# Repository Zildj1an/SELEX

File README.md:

# SELEX Process with Artificial Intelligence 👨‍🔧

## [0] Introduction 📄

This was a long project that involved:

 * [1] The robotic automatization of biotechnological protocols.
 
      All the custom hardware design can be found at OT_Robot/harware_design.
 * [2] The usage of Artifical Intelligence.
 * [3] A search engine.
 * [4] A tool to migrate WordPress websites to the iGem servers.
 * [5] And many, many custom hardware.

You can find information on installation and usage at the end [5] and our <a href = "https://2019.igem.org/Team:MADRID_UCM/Hardware">website</a>.

## [1] Biotechnological Designs 🔬

Folder OT_Robot contains biotechnological protocols for obtaining trained libraries of DNA aptamer molecules automated with the Opentrons OT-2 robot. This protocol is part of our contribution to the 2019 iGEM international biotechnology competition. For the thermocycler we built the Ninja-PCR(original from [hisashin](https://github.com/hisashin/NinjaPCR/)). More information about the entire project can be found in our <a href = "https://2019.igem.org/Team:MADRID_UCM/Landing">website</a>.

Aptamers are a cutting-edge technology that is revolutionizing biotechnology, from biosensing to synthetic biology. Aptamers are single-strand DNA molecules that hold nature’s most important information: our genetic code. But instead of using DNA for carrying information, our aptamers depend on DNA’s 3-dimensional shape. 

We genetically engineer this shape to take hold of and mesh with our target molecule. DNA’s unique role in nature gives aptamers amazing characteristics, making them robust, stable, and cheap to produce. 

The small-sized thermal cycler is controlled via motherboard Ninja-PCR Arduino-alike, as shown above, manually welded, whose code is in NinjaPCR [folder](https://github.com/Zildj1an/SELEX/tree/master/NinjaPCR). You can update a new binary since ESP8266 SystemOnChip includes the TCP/IP stack. We also recommend the usage of an external Raspberry Pi to uninterruptedly provide the robot with Wi-Fi. You can find more information about usage at [5].

## [2] Artificial Intelligence Algorithm: GAN network 🤖

We also did an **Artificial Intelligence algorithm** to predict the optimal DNA molecule shapes. It is a Generative adversarial network, divided in two neuronal networks: the Generative and the Discriminative. CNN nets are used. 

## [3] iGem Search Engine 🔍 

In addition, you can use our Search Engine for words in previous or this year's team's websites. This is a python search engine with GUI for searching words in each competition year and team's website.

# [4] A tool to migrate WordPress websites to the iGem servers.

We also developed a tool to make life easier to web page developers at the iGem competition. You can use WordPress templates to develop your site and then migrate it easily with this multi-threaded script located at Tool_Migrate folder.

To run the script you can do:

```
$ bash treatment.sh [url_1] -nm - - [url_2]
```

Some additional options are available, feel free to navigate throw our code!

# [5] Hardware Design 🔋 

## Potentiostat

To assemble the potentiostat, first you should send to manufacture the PCB, in our instance we sent it to JLPCB (https://jlcpcb.com/) and buy the components listed on the Bill of Materials file. After that, you should solder those materials on the PCB. You can also request them to solder the components, if they have them.

Any team could reproduce this potentiostat sending the gerber and the NC Drill files to the manufacturer.

Regarding to the case, we designed it with a 3D modelling software, and we cut the flat faces in methacrylate with a laser cutter machine and otherwise we printed it with a 3D printer.

The PCB was made with the Altium Designer software. Altium can export PCB and schematic files as ACCEL-ASCII files. With these files you can import them to Eagle.

## Fluorimeter
To assemble the fluorimeter, you should send to manufacture the PCB, for instance we sent it to JLPCB (https://jlcpcb.com/) and buy the components listed on the Bill of Materials file. After that, you should solder those materials on the PCB. You can also request them to solder the components, if they have them.

Any team could reproduce this fluorimeter sending the gerber and the NC Drill files to the manufacturer. The PCB was made with the Altium Designer software. Altium can export PCB and schematic files as ACCEL-ASCII files. With these files you can import them to Eagle.

In relation to the case, we designed it with a 3D modelling software, and we cut the faces in methacrylate with a laser cutter machine.

## Wax Module
Wax Module
To assemble the Wax Module, you should send to manufacture the PCB, in our instance we sent it to JLPCB (https://jlcpcb.com/) and buy the components listed on the Bill of Materials file. After that, you should solder those materials on the PCB. You can also request them to solder the components, if they have them.

Any team could reproduce this module sending the gerber and the NC Drill files to the manufacturer.

The PCB was made with the Eagle software. To generate the necessary files, you can follow the JLPCB guide (https://support.jlcpcb.com/article/43-how-to-export-eagle-pcb-to-gerber-files).

In relation to the case, we designed it with a 3D modelling software, and we cut the faces with a laser cutter and the part where the resistances are located, was printed with an aluminium printer. Also, the part where the stamps are placed can be printed with a 3D printer.

## PCR, Thermal Modules
To assemble the NinjaPCR, you can make it yourself following the instructions written on their webpage or buy it (https://ninjapcr.tori.st/en/index.html).

To assemble the Thermal Module, you can send to manufacture the PCB, in our instance we sent it to JLPCB (https://jlcpcb.com/) and buy the components listed on the Bill of Materials file. After that, you should solder those materials on the PCB. You can also request them to solder the components, if they have them. The other option you could buy it from their webpage.

In relation to the case, we redesigned the NinjaPCR case with a 3D modelling software, and we cut the faces with a laser cutter in methacrylate and in wood. 

We redesigned it because we used another fan.

## Shaker Module
To assemble the Shaker Module, you should send to manufacture the PCB, in our instance we sent it to JLPCB (https://jlcpcb.com/) and buy the components listed on the Bill of Materials file. After that, you should solder those materials on the PCB. You can also request them to solder the components, if they have them.

Any team could reproduce this module sending the gerber and the NC Drill files to the manufacturer.

The PCB was made with the Eagle software. To generate the necessary files, you can follow the JLPCB guide (https://support.jlcpcb.com/article/43-how-to-export-eagle-pcb-to-gerber-files).

In relation to the case, we designed it with a 3D modelling software, and we printed the module with a 3D printer.

We also designed some PCBs from ourselves to make things easier and make them fit in the robot. We used a 3D-printer for some of our designs to store Eppendorf and Falcon tipracks. We also deisgned a PCB for a potenciostat microcontroller Teensy 3.0 and an auxiliar thermic module to cool to 4 degrees Celsius, and so on.

The 3D-designs will are available at the folder OT_Robot/hardware_design

## [6] Installation and Usage ❓

Our project has a lot of software involved, including:

1. A graphical Search Engine for words in websites of previous years of iGem:
   
You can run it from your terminal using:
```
$ python search.py
```
You might have some dependencies not installed, you just need to do:
```
$ sudo pip install <dependencies>	
```

2. The Aptamer Folding:

In the folder DB_Creation, execute (if you use Mac or Linux), for terminal:
```
$ python DB_Creation_Terminal.py
```
You can also speed things up with threads with bash run_several.sh, but be aware that you would need to modify the absolute path to the Rosetta software.

In the folder GAN_Network, from terminal:
```
$ python Main.py
```
Other files that could be used:

3D_structure_creation_in_pdb.py Creates only one PDB for the DDBB (testing puposes)

GAN_Network.py (Same thing as GAN_Network folder but in one file)

3. OT_Robot protocols

It contains tons of biotechnological protocols automated for the Opentrons OT2 robot in Python. The most important one is the SELEX process. To run these protocols you just need to drug and drop the protocols into the OT2 app.

You can also find in here the hardware design.

You can clone this repo or download the zip. Make sure all the dependencies are covered. First line is for installation of pip at most Linux distributions.

```
$ sudo apt install python-pip || pacman -S python-pip
$ sudo pip install opentrons subprocess time os
```
The robot uses the audio robot.mp3 and gets it from Robot Raspberry's /mnt/usbdrive/ (put it there or edit the location).
You can load the protocol in the Opentrons application, available <a href = "https://opentrons.com/ot-app">here</a>.
We also recommend the usage of an external Raspberry Pi to uninterruptedly provide the robot with Wi-Fi. Once you have stablished the Wi-Fi network at the Raspberry, you can connect the Robot too:

```
# nmcli dev wifi connect <userSSID> password <passwdSSID>
```
After the last update of the Robot -by the time this is written- the SSH connection has changed and now you need to exchange with it a public key for a more secure connection. Then when connected the robot will request the passphrase, at least the first time. Here is how you create the public key (you probably already have one):

```
$ ssh-keygen
Generating public/private rsa key pair.
Enter file in which to save the key (/home/.ssh/id_rsa):
/home/pepe/.ssh/id_rsa already exists.
Overwrite (y/n)?
Enter passphrase (empty for no passphrase):
Your identification has been saved in /home/.ssh/id_rsa.
Your public key has been saved in /home/.ssh/id_rsa.pub.
The key fingerprint is:
a9:49:2e:2a:5e:33:3e:a9:de:4e:77:11:58:b6:90:26 pepe@remote_host
The key's randomart image is:
+--[ RSA 2048]----+
|     ..o         |
|   E o= .        |
|    o. o         |
|        ..       |
|      ..S        |
|     o o.        |
|   =o.+.         |
|. =++..          |
|o=++.            |
+-----------------+
```

## Authors
* [Pablo Villalobos](https://github.com/pablo-vs)
* [Carlos Bilbao](https://github.com/Zildj1an)
* [Ana Matesanz](https://github.com/anamatesanz)
* [Irene Guardiola](https://github.com/Irene-G)
* Francisco Javier Quero

## License
This project's source code is licensed under the GNU-GPL License - see the <a href="https://github.com/Zildj1an/SELEX/blob/master/LICENSE">LICENSE.md</a> file for details. The other parts of the project have the Creative Commons license, as stated in the competition guidelines.

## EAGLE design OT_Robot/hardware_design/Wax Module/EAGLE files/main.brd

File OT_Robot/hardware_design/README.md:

# Hardware Design

## Potentiostat

To assemble the potentiostat, first you should send to manufacture the PCB, in our case we sent it to JLPCB (https://jlcpcb.com/), and buy the components listed on the Bill of Materials file. After that, you should solder those materials on the PCB. You can also request them to solder the components, if they have them.
To be able to plug the electrode, we welded three pins into it.

Any team could reproduce this potentiostat sending the gerber and the NC Drill files to the manufacturer.

Regarding to the case, we designed it with a 3D modelling software, and we cut the flat faces in methacrylate with a laser cutter machine and otherwise we printed it with a 3D printer.

The PCB was made with the Altium Designer software. Altium can export PCB and schematic files as ACCEL-ASCII files. With these files you can import them to Eagle.

## Fluorimeter
To assemble the fluorimeter, you should send to manufacture the PCB, for instance we sent it to JLPCB (https://jlcpcb.com/) and buy the components listed on the Bill of Materials file. After that, you should solder those materials on the PCB. You can also request them to solder the components, if they have them.

Any team could reproduce this fluorimeter sending the gerber and the NC Drill files to the manufacturer. The PCB was made with the Altium Designer software. Altium can export PCB and schematic files as ACCEL-ASCII files. With these files you can import them to Eagle.

In relation to the case, we designed it with a 3D modelling software, and we cut the faces in methacrylate with a laser cutter machine.

## Wax Module

To assemble the Wax Module, you should send to manufacture the PCB, in our instance we sent it to JLPCB (https://jlcpcb.com/) and buy the components listed on the Bill of Materials file. After that, you should solder those materials on the PCB. You can also request them to solder the components, if they have them.

Any team could reproduce this module sending the gerber and the NC Drill files to the manufacturer.

The PCB was made with the Eagle software. To generate the necessary files, you can follow the JLPCB guide (https://support.jlcpcb.com/article/43-how-to-export-eagle-pcb-to-gerber-files).

In relation to the case, we designed it with a 3D modelling software, and we cut the faces with a laser cutter and the part where the resistances are located, was printed with an aluminium printer. Also, the part where the stamps are placed can be printed with a 3D printer.
The first design was made with PLA, however it got too hot and we melted it, thus the next design was made in aluminium, additionally it is a better conductor of heat. 

## PCR, Thermal Modules

To assemble the NinjaPCR, you can make it yourself following the instructions written on their webpage or buy it (https://ninjapcr.tori.st/en/index.html). 
To automatize the lid you just have to print the Engine_Support 3D model and buy the DS3225 25Kg servomotor.

The PCB of the Thermal Module is assembled in the same way as the potentiostat.
The other option is buying it from their webpage.

In relation to the case, we redesigned the NinjaPCR case with a 3D modelling software, and we cut the faces with a laser cutter in methacrylate and in wood. We had to redesign the case because the fan we used was too big in comparition to the one the NinjaPCR uses.
At the beginnig we bougth the ARCTIC Freezer 11 LP fan, but it did not dissipate enough heat and the peltier cell started getting hot, therefore we changed it to SilverStone SST-AR06. With this one was enough, but at some point it broke down and we finally changed it to ARCTIC F12 - 120 mm.

## Shaker Module

The PCB of the Shaker Module is assembled in the same way as the potentiostat. Like the Wax Module, most of the components were soldered by the manufacturer.

The PCB was made with the Eagle software. To generate the necessary files, you can follow the JLPCB guide (https://support.jlcpcb.com/article/43-how-to-export-eagle-pcb-to-gerber-files).

In relation to the case, we designed it with a 3D modelling software, and we printed the module with a 3D printer.

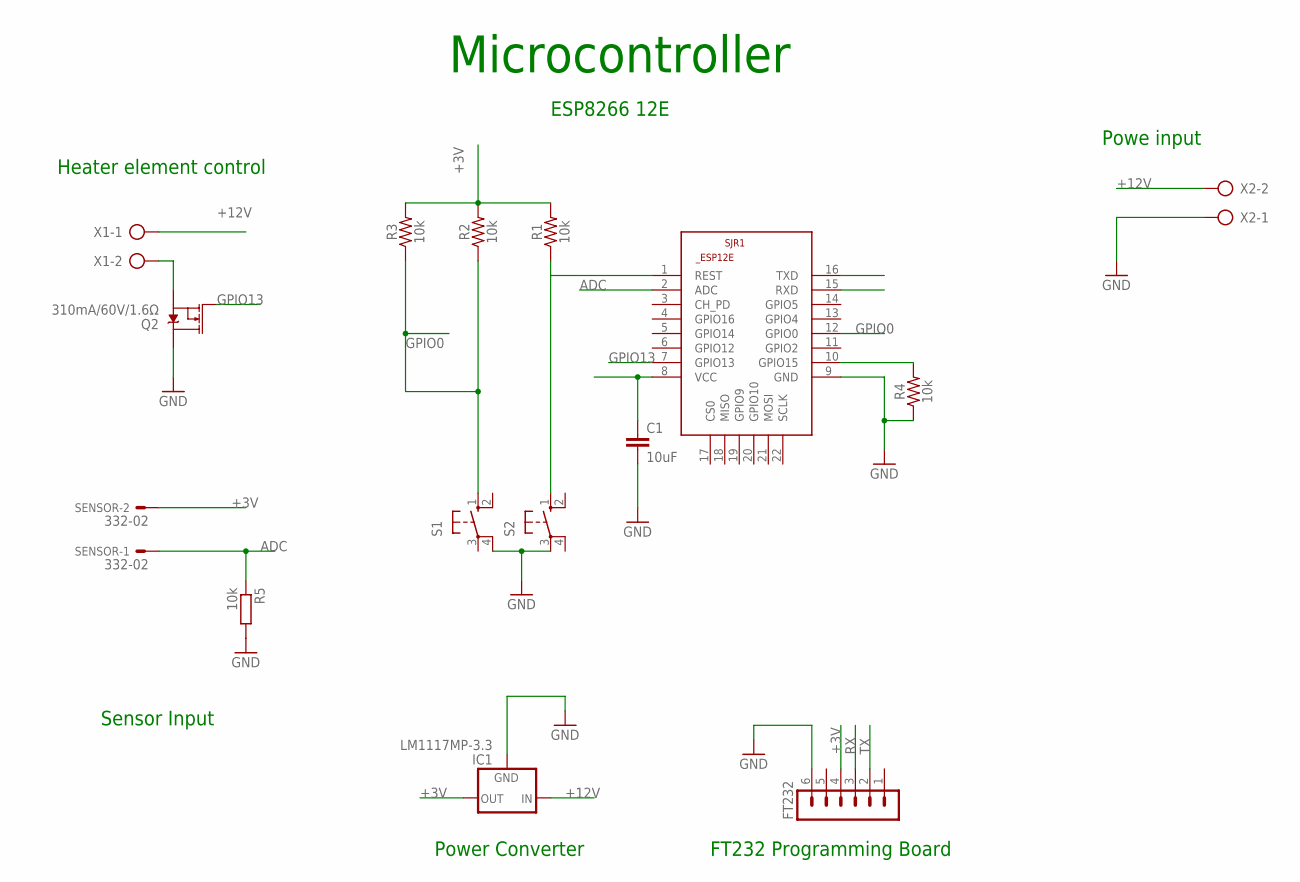
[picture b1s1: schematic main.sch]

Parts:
C1: 10uF; C1206
FT232: MA06-1
IC1: LM1117MP-3.3; SOT223
Q2: 310mA/60V/1.6Ω; SOT323
R1, R2, R3, R4: 10k; 0603
R5: 10k; R1206
S1, S2: 10-XX; B3F-10XX
SENSOR: 332-02
SJR1: ESP8266-12EESP12E; ESP8266-ESP12E
X1, X2: AK500/2

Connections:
+3V: C1.1, FT232.4, IC1.2 (OUT), IC1.4 (OUT), R1.2, R2.2, R3.2, SENSOR.2, SJR1.8 (VCC)
+12V: IC1.3 (IN), X1.1, X2.2
ADC: R5.1, SENSOR.1, SJR1.2 (ADC)
GND: C1.2, FT232.6, IC1.1 (GND), Q2.3 (D), R4.1, R5.2, S1.4 (P1), S2.3, SJR1.9 (GND), X2.1
GPIO0: R2.1, R3.1, S1.1 (S), SJR1.12 (GPIO0)
GPIO13: Q2.1 (G), SJR1.7 (GPIO13)
unnamed: Q2.2 (S), X1.2
unnamed: R1.1, S2.1 (S), SJR1.1 (REST)
unnamed: R4.2, SJR1.10 (GPIO15)
RX: FT232.3, SJR1.15 (RXD)
TX: FT232.2, SJR1.16 (TXD)

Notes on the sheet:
Microcontroller
ESP8266 12E
FT232 Programming Board
Power Converter
Sensor Input
Heater element control
Powe input

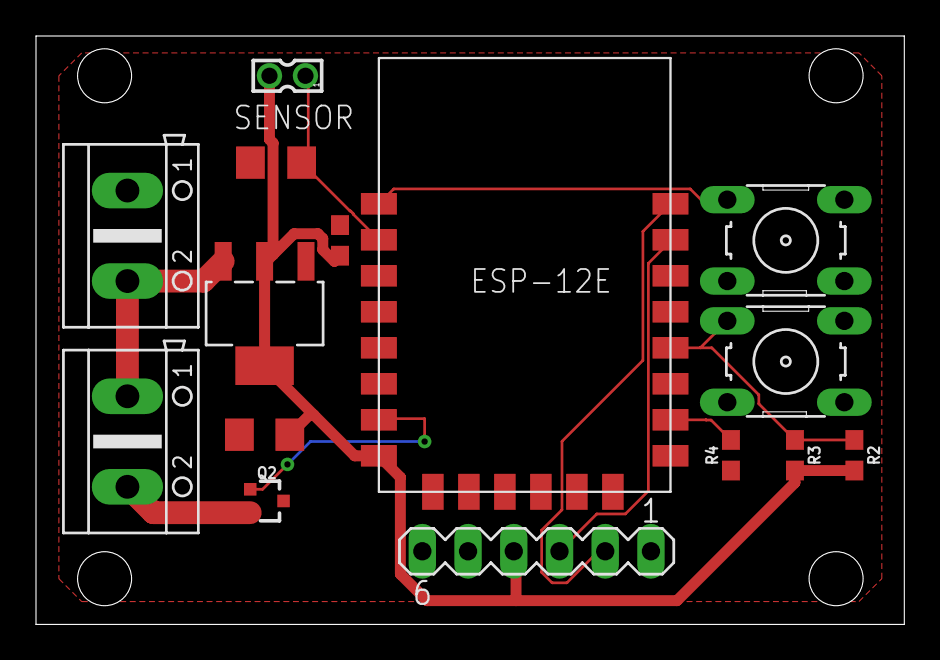
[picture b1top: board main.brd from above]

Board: 2 copper layers, 48.2 x 32.7 mm, 15 parts (0 on the bottom side), 11 nets.

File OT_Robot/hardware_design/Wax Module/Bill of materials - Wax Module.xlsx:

Aegis Wax Module BOM
Component | Description | Digi-Key Part # | Designator | Datasheet URL | Quantity | Price ($) | Subtotals ($)
Caps
10UF | CAPACITOR, European symbol |  | C1 | pdf/pdf/120370/ETC1/CC1206.html | 1 | 0.08 | 0.08
Resistors
10KOhm | 10KOHM-0603-1/10W-1% |  | R1, R2, R3, R4,R5 |  | 5 | 1.6000000000000001E-3 | 8.0000000000000002E-3
ICs
LM1117MP-3.3 | 800mA Low-Dropout Linear Regulator | LM1117MP-3.3/NOPBCT-ND | IC1 | http://www.ti.com/lit/ds/symlink/lm1117.pdf | 1 | 1.1399999999999999 | 1.1399999999999999
MOSFET-NCH-2N7002PW | N-channel MOSFETs |  | Q2 | https://docs-emea.rs-online.com/webdocs/1206/0900766b812062e7.pdf | 1 | 0.27 | 0.27
ESP12E | Microcontroller + Wifi |  | SJR1 |  | 1 | 1.1599999999999999 | 1.1599999999999999
Other Supplies
Switch | OMRON SWITCH |  | S1, S2 | https://www.alldatasheet.com/datasheet-pdf/pdf/206803/OMRON/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 | 2 | 0.25 | 0.5
 |  |  |  |  |  | TOTAL: | 3.1579999999999999 | $

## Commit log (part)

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2019-07-12 Starting
2019-07-12 more
2019-07-12 custom labware
2019-07-12 authors
2019-07-12 Ninja PCR full code and binary
2019-07-13 Preliminary project's website
2019-07-15 starts doing something...
2019-07-16 problem with array
2019-07-17 sound
2019-07-17 audio
2019-07-17 GET requests
2019-07-17 First step
2019-07-18 more aux
2019-07-19 some more
2019-07-19 need info
2019-07-19 json
2019-07-22 Added NinjaPCR driver
2019-07-22 amplify
2019-07-23 Modified pcr driver
2019-07-23 NinjaPCR driver: + Added support for sending commands and example program
2019-07-24 Full PCR protocol, first version
2019-07-26 Pcr graph, ninja driver, calibration test
2019-07-26 test.py well calibrated
2019-07-26 folder
2019-07-26 DNA Amplification
2019-07-26 Create LICENSE
2019-07-26 debug msg in file
2019-07-29 tabs
2019-07-29 debug file
2019-08-01 Spaces
2019-08-01 coating
2019-08-01 Added eppendorf dimensions
2019-08-01 Added Falcon dimensions
2019-08-01 Corrected eppendorf dimensions' units
2019-08-01 database list
2019-08-01 ascii art
2019-08-01 Commented database deletion
2019-08-02 Updated protocols
2019-08-02 More coating
2019-08-05 Changes for 300ul
2019-08-07 Tincion Dyeing
2019-08-08 Good Values Robot
2019-08-09 Dyeing FINISHED
2019-08-09 Dyeing
2019-08-12 Merge
2019-08-13 - Added separacion.py - Updated tincion and coating - Updated NinjaPCR driver and added thermal module driver
2019-08-13 - Updated ninja driver: support for different labwares for PCR and TempDeck - separacion.py now uses the P300_Single pipette
2019-08-13 - Coating now uses the P300_Single pipette - Updated separacion - Updated tincion
2019-08-13 Deleted rubbish
2019-08-19 Test separacion
2019-08-19 discomment and tabs
2019-08-19 Separacion CHANGED
2019-08-19 Inner functions separacion
2019-08-20 Corregir fallos separacion
2019-08-20 For, delays
2019-08-21 Potenciostat
2019-08-21 New coating
2019-08-21 Elona
2019-08-21 Corrected elona and coating
2019-08-22 DNA molecule
2019-08-22 Updated elona
2019-08-26 Cambios elona
2019-08-26 Restore
2019-08-26 ELONA FINAL FORM
2019-08-26 Functions to elona
2019-08-26 Small corrections
2019-08-27 Elona corrections
2019-08-27 new protocol
2019-08-27 New protocol almost finished
2019-08-27 New protocol finished
2019-08-28 New elona
2019-08-28 tabs protocol
2019-08-28 error
2019-08-28 error storage
2019-08-28 Xtreme Ngineering effort
2019-08-28 imgs
2019-08-28 Elona adjustments
2019-08-28 Removed garbage
2019-08-29 New version of cells separation
2019-08-29 Teensy
2019-08-29 Improvement
2019-08-29 New version cell
2019-08-29 Version of separate cells
2019-08-29 Elona: change tips while transfering tween to plate
2019-08-29 - Added teensy DAC control - Added mix_after in separation_cells - Elona corrections
2019-08-31 Removed trash
2019-09-02 Gitignore
2019-09-04 - Elona changes - Separation_cell changes - Uploaded rodeostat libraries to teensy-loader/libraries
2019-09-06 Final separations
2019-09-06 Separation correction
2019-09-10 iGem search mechanism
2019-09-10 Search mechanism
2019-09-11 Threaded
2019-09-11 three threads
2019-09-11 Threads
2019-09-11 Threads and letters
2019-09-12 error handling and url file
2019-09-12 Error handling and file
2019-09-12 works
2019-09-12 Teensy potentiostat code
2019-09-13 New version
2019-09-13 Teensy changes
2019-09-13 Tabs & shit
2019-09-13 Working teensy setup
2019-09-13 GUI start
2019-09-13 Alphabetical team name distribution script
2019-09-13 Alpha addition
2019-09-13 Results_sabado
2019-09-14 Basic GUI finished
2019-09-14 GUI working
2019-09-14 resultados 2016
2019-09-16 Latex affinity protocol
2019-09-17 Resultados 2013
2019-09-17 Latex affinity
2019-09-18 Elona changes
2019-09-24 Search res_2018
2019-09-26 Latest NinjaPCR and NinjaTempDeck code
2019-09-26 Ninja readmes
2019-09-26 Ninja readme corrections
2019-09-26 Teensy readme
2019-09-27 Cera
2019-10-15 Cera.py
2019-10-17 All the software
2019-10-18 Hardware Design
2019-10-18 hw design
2019-10-18 tutorial
2019-10-18 design
2019-10-19 New HW and design
2019-10-20 Solved HW issues
2019-10-21 Markdown
2019-10-21 Syntax
2019-10-21 New images
2019-10-21 readme
2019-10-21 New tool for migrating WordPress website
2019-11-12 all members
2019-11-24 lo voy a cambiar
2019-11-24 delete rside
    lo voy a cambiar
2019-11-24 delete side
    lo voy a cambiar
2019-11-24 delete top
    lo voy a cambiar
2019-11-24 delete board
    lo voy a cambiar
2019-11-24 delete inside
    lo voy a cambiar
2019-11-24 delete stamp1
    lo voy a cambiar
2019-11-24 delete stamp2
    lo voy a cambiar
2019-11-24 delete stamp3
    lo voy a cambiar
2019-11-24 delete heater
    lo voy a cambiar
2019-11-24 delete cover-top
    lo voy a cambiar
2019-11-24 delete cover-back
    lo voy a cambiar
2019-11-24 delete cover-front
    lo voy a cambiar
2019-11-24 delete cover-side
    lo voy a cambiar
2019-11-24 delete cover-bottom
    lo voy a cambiar
2019-11-24 delete heatsink-hang
    lo voy a cambiar
2019-11-24 delete body-top
    lo voy a cambiar
2019-11-24 delete peltier
    lo voy a cambiar
2019-11-24 delete body-front
    lo voy a cambiar
2019-11-24 delete body left
    lo voy a cambiar
2019-11-24 delete body-back
    lo voy a cambiar
2019-11-24 delete body bottom
    lo voy a cambiar
2019-11-24 delete base
    lo voy a cambiar
2019-11-24 delete back
    lo voy a cambiar
2019-11-24 delete bottom
    lo voy a cambiar
2019-11-24 delete left
    lo voy a cambiar
2019-11-24 delete rigth
    lo voy a cambiar
2019-11-24 delete heatsink
    lo voy a cambiar
2019-11-24 delete pcbwood
    lo voy a cambiar
2019-11-24 piezas sustituidas

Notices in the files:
README.md:
GPLv3 license
parts and their libraries:
SparkFun-DiscreteSemi: Licensing: Creative Commons ShareAlike 4.0 International - https://creativecommons.org/licenses/by-sa/4.0
